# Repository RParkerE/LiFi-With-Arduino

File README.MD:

# LiFi Communication System

## Table Of Contents
1. [Introduction](#introduction)
2. [File Architecture](#file-architecture)
3. [GUI](#gui)
4. [State Machine](#state-machine)
    1. [Sender States](#sender-states)
    2. [Receiver States](#receiver-states)
6. [Firmware](#firmware)
7. [Hardware](#hardware)
8. [Further Development](#further-development)

### Introduction
The aim of this project is to design and build a demonstration product of a low cost LiFi communication system for the 
home. The system will consist of a module that encodes and modulates a digital signal into an LED transmitter/receiver 
pair through the medium of air over a reasonable distance.

### File Architecture
```
LiFi
├─── files
│     └─── out.txt
├─── firmware
│     ├── bidirectional
│     │   └── bidirectional.ino
│     ├── driver_receive
│     │   └── driver_receive.ino
│     ├── driver_send
│     │   └── driver_send.ino
│     ├── lib
│     │   ├── Arduino-GPIO
│     │   └── DueTimer
├─── hardware
│     ├─── LiFiShieldV2.brd
│     ├─── LiFiShieldV2.sch
│     └─── README.MD
├─── lib
│     ├─── fsm.py
│     ├─── LiFiGUI.py
│     ├─── main.py
│     ├─── my_states.py
│     ├─── Receiver.py
│     ├─── Sender.py
│     ├─── serial_connect.py
│     └─── state.py
├─── README.md
└─── requirements.txt
```

### GUI
The GUI for the driver is built using TkInter. All of the functions used in constructing thr GUI are in LiFiGUI.py (which also
has a thread for checking data on the serial line). For more information on GUI development with TkInter you can look at the 
following:

[TkInter Documentation](https://docs.python.org/3/library/tk.html)

[TkInter Wiki](https://wiki.python.org/moin/TkInter)

[TkInter Tutorial](https://likegeeks.com/python-gui-examples-tkinter-tutorial/)

### State Machine

This state machine tracks and models the life cycle of the driver.

```
.-> Receiver ---- "SEND BUTTON PUSHED" ---> Sender
|     |   ^_________________________           |
| "DATA RECEIVED"                   |          |
|     |                             |          |
| Parse Meta                        |     Create Meta
|     |                             |          |
| Receive Data<--------------.      |      Send Data<---.
|   __|____________          |      |          |        |    
|  |               |         |      |        Wait       |
.-"NO ERROR"     "ERROR(S)"--.      |     ____|______   |
                                    |    |           |  |
                                  "DONE PACKET"   "RESEND"
```

#### Sender States
There are 4 states that are associated with the Sender driver:

##### Sender
This state initializes the driver as the sender side and pushes the state machine to the next state

##### Create_Meta
This state takes the file data and creates a 64 byte meta packet include a 4 byte index [0x00000000], 15 bytes of data
[4 bytes - number of packets, 1 byte - 0 padding at end of file, 10 bytes - file extension] + 41 bytes of 0s for 
padding, and a final 4 bytes for a crc checksukm. Once this packet is created, it is written to the serial port using 
pySerial and pushes the state machine to the next state.

##### Send_Data
This state takes the data in the file, splits it into 56 byte chunks (or less for the last packet which is padded with 
0s to make it 56 bytes) and add a 4 byte header which increases sequentially, and a 4 byte crc checksum for each 56 
byte chunk. This is looped over and each individual packet is written to the serial port using pySerial. It then pushes 
the state machine to the next state.

##### Wait
This state waits for a reply from the receiver side. If a Finish Packet is received, then it moves the state machine 
back to the Receive state. If a Resend Packet is received, then it moves the state machine back to Send_Data, and 
resends the packets with errors.

#### Receiver States
There are 3 states that are associated with the Receiver driver:

##### Receiver
This state initializes the driver as the receiver side and is the default state

##### Parse_Meta
This state reads in 64 byte, the first full packet, from the serial port using pySerial. It makes sure the index is 0 
and the crc checksum calculated with the received data and the crc checksum that was received are equal to one another.
If these checks are both true, the data is then parsed and stored. The state machine is then pushed to Receive_Data.

##### Receive Data
This state reads in 64 bytes at a time from the serial port using pySerial. This is then split into index, data, and 
checksum. If the calculated and received checksum are equal, the data is then pushed to an array at the index that 
packet corresponds to, otherwise "ERROR" is written to the array at the corresponding index. After all data is read and
has been checked, if there are no errors, the data is written to a file and the Finish Packet is sent and the state
machine is pushed to the Receiver state. Otherwise the Resend packet will be sent with up to 14 indices that had errors
and the state machine is pushed back to the Receive_Data state.

### Firmware

#### Bidirectional
Sets DAC0 voltage, Serial, and Serial1.

If Serial is available (Sending) write to Serial1. If Serial1 is available (Receiving) write to Serial.

#### Driver_Receive & Driver_Send
These are deprecated. Use the bidirectional code instead.

### Hardware
Refer to the README within the subdirectory

### Further Development
There are many areas which can be further developed. Some ideas for what could be done are listed below:

- Create a more sophisticated packet system
- Optimize for distance and speed
- Update driver to allow for more than file transfers
    - Possibly be able to connect to internet
- Move from point-to-point communication to a hub-client type communication

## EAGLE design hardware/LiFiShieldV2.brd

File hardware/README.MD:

## Things To Note
- LM311N Part Is To Be Replaced With LT1016
  - They share the same footprint, pinout used is for the LT1016

R1 -> 36 Ω

R2 -> 160 kΩ

R3 -> 22 kΩ

R4 -> Feedback Resistor (variable value for optimization)

C1 -> 1 μF

C2 -> .047 μF

C3 -> Feedback Capacitor (variable value for optimization)

C4 -> 1 pF

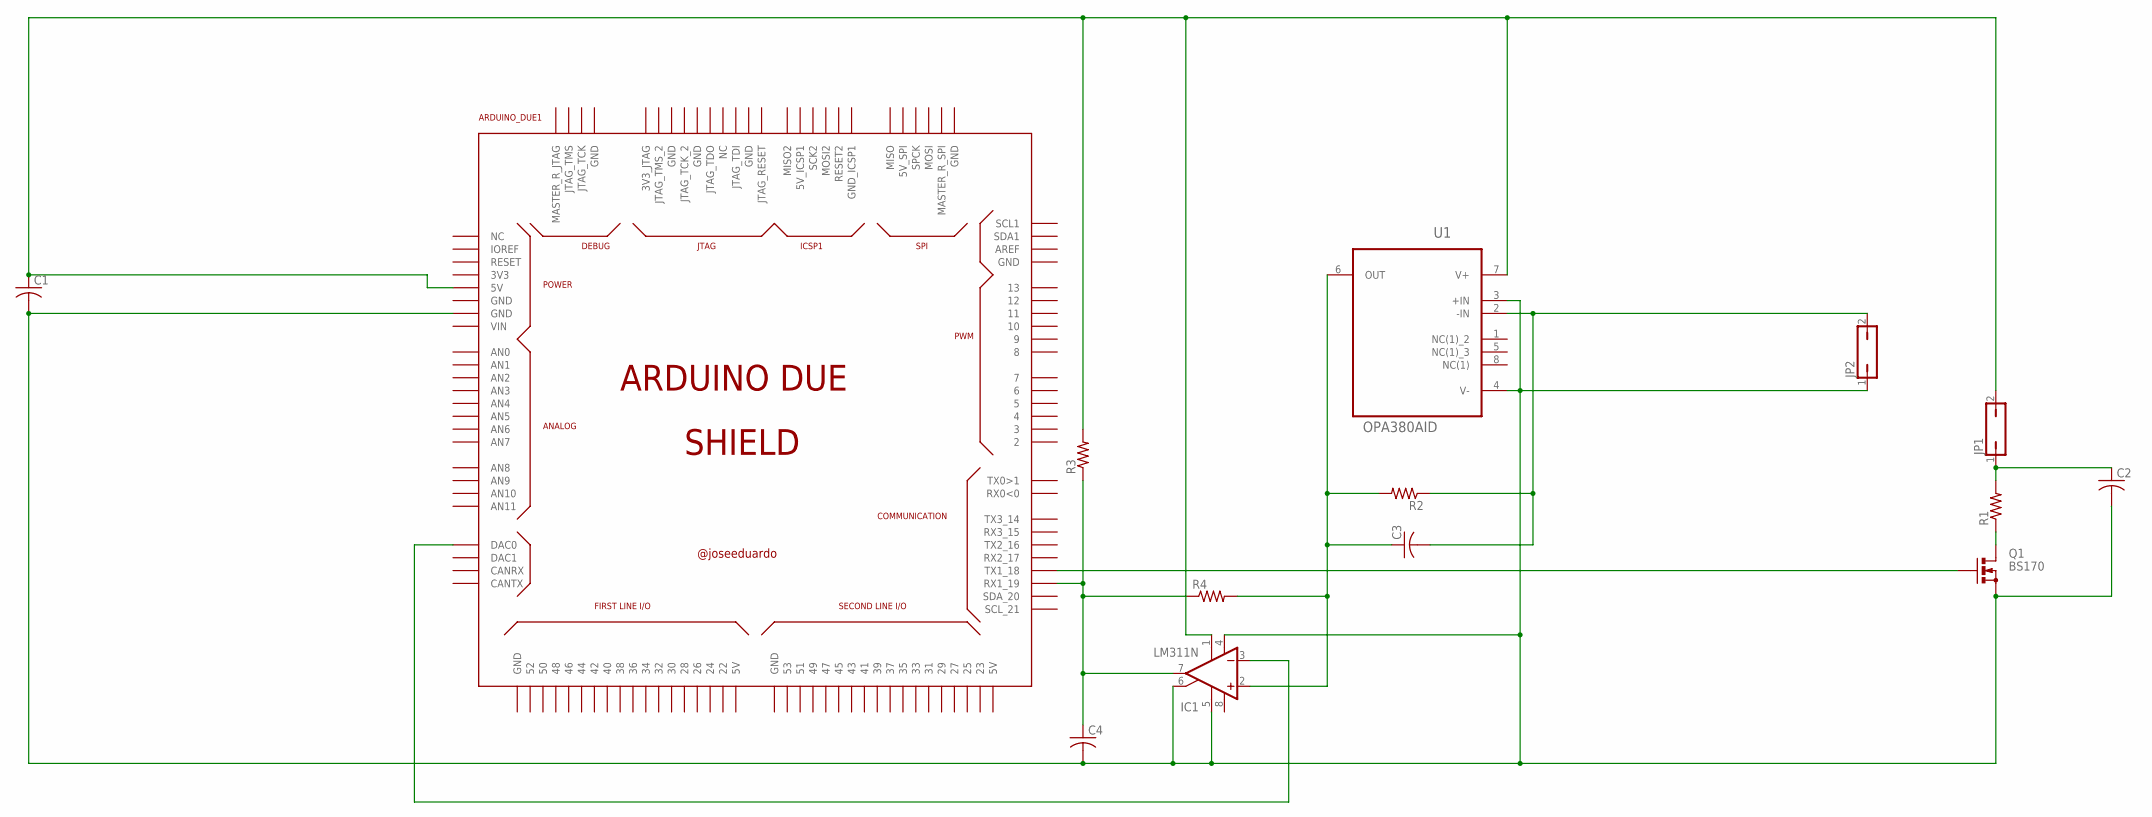
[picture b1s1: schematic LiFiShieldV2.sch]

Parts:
ARDUINO_DUE1: ARDUINO_DUE_SHIELD
C1, C2, C3, C4: C-US050-055X075; C050-055X075
IC1: LM311N; DIL08
JP1, JP2: JP1Q; JP1
Q1: BS170; SOT54E
R1, R2, R3, R4: R-US_0204/7; 0204/7
U1: OPA380AID; SOIC127P600X175-8N

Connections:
unnamed: C2.1, JP1.1, R1.2
unnamed: Q1.D, R1.1
unnamed: ARDUINO_DUE1.DAC0, IC1.3 (-IN)
unnamed: ARDUINO_DUE1.18 (TX1_18), Q1.G
unnamed: C3.1, IC1.2 (+IN), R2.2, R4.2, U1.6 (OUT)
unnamed: C3.2, JP2.2, R2.1, U1.2 (-IN)
unnamed: ARDUINO_DUE1.19 (RX1_19), C4.1, IC1.7 (OUT), R3.1, R4.1
unnamed: ARDUINO_DUE1.GND_1 (GND), C1.2, C2.2, C4.2, IC1.4 (V-), IC1.5 (ON), IC1.6 (ON/STR), JP2.1, Q1.S, U1.3 (+IN), U1.4 (V-)
unnamed: ARDUINO_DUE1.5V0 (5V), C1.1, IC1.1 (GND), JP1.2, R3.2, U1.7 (V+)
V+: IC1.8 (V+)

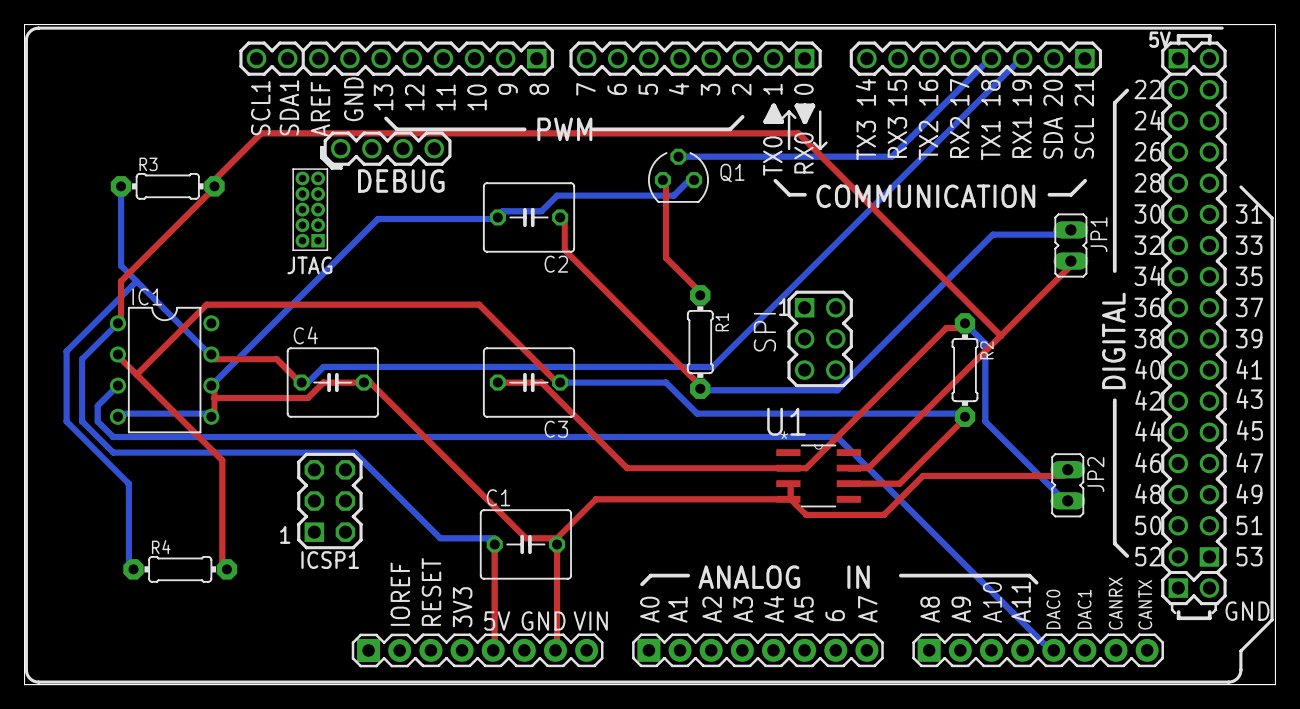
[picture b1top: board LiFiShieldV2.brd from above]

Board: 2 copper layers, 102.0 x 53.8 mm, 14 parts (0 on the bottom side), 9 nets.

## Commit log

2019-01-24 Initial Commit
    Initial Code From CDR
2019-01-24 Change Custom CRC To zlib.crc32
    Change our custom CRC function to use zlib.crc32 instead
2019-02-07 Add Gui, Tested Sender
2019-02-07 Rename Reciever.py to Receiver.py
2019-02-07 full gui capabilities.
2019-02-19 Send .jpg/.pdf/etc w/o Arduino
2019-02-21 Speak W/ Arduino, Cross Platform, Manual/Automatic
2019-02-21 bug fixes
2019-02-21 Arduino Firmware
2019-02-21 Fixed Transmission Of Only 1s
2019-02-21 Rest Time Added For Arduino
2019-02-21 loop over packets
2019-02-27 Modularize Code, Create FSM
2019-02-27 Fix tkinter Error About X11
2019-02-27 Rename LiFiGUI.py to lib/LiFiGUI.py
2019-02-27 Rename Receiver.py to lib/Receiver.py
2019-02-27 Rename Sender.py to lib/Sender.py
2019-02-27 Rename fsm.py to lib/fsm.py
2019-02-27 Rename my_states.py to lib/my_states.py
2019-02-27 Rename serial_connect.py to lib/serial_connect.py
2019-02-27 Rename state.py to lib/state.py
2019-02-27 Rename driver_receive.ino to firmware/driver_receive.ino
2019-02-27 Rename driver_send.ino to lib/driver_send.ino
2019-02-27 Rename lib/driver_send.ino to firmware/driver_send.ino
2019-02-28 Added Setter and Getter Methods
2019-02-28 Changed receiver_driver to a class, added getter/setter
2019-02-28 Update Sender_test
2019-02-28 Update test files
2019-02-28 Updated FSM Flow
2019-02-28 Add main.py
2019-03-04 Classify Main, Add GUI Loop
2019-03-04 Fix Connect Button Display
2019-03-05 state transisitions, sender..
2019-03-05 Sender/Receiver default filename value added
2019-03-06 Added functions for resend, parse, finish
2019-03-07 update file path
2019-03-07 resend,finish packets
2019-03-07 firm update
2019-03-07 Cross Platform File Path
2019-03-07 Cross Platform Path Fix
2019-03-08 State Transitions Working For Send & Receive
2019-03-08 State Transition Updates
2019-03-18 Buggy Code, Pushed So Everyone Is On Same Page
2019-03-19 Fixed Whitespace Issues And Still Working On Bugs
2019-03-21 Debug More
2019-03-23 No Longer Using
2019-03-23 Stable Dev Version
2019-03-23 Threading Moved To LiFiGUI
2019-03-23 Fix Delay Issue
2019-03-23 Bidirectionality Works In Driver
2019-03-27 Fixed State Transitions
2019-03-27 DAC capabilities
2019-03-27 State Transition Edit
2019-04-03 Change flag from int to bool
2019-04-04 Fixed Issue 1
2019-04-04 Catch OSError on Serial Disconnect
2019-04-04 fixed delay
2019-04-05 Add comments
2019-04-08 Remove unused imports and arguments
2019-04-23 Demo Day Code Changes
